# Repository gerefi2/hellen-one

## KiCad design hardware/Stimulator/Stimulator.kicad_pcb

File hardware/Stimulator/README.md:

Stimulator
==========

gerefi Stimulator

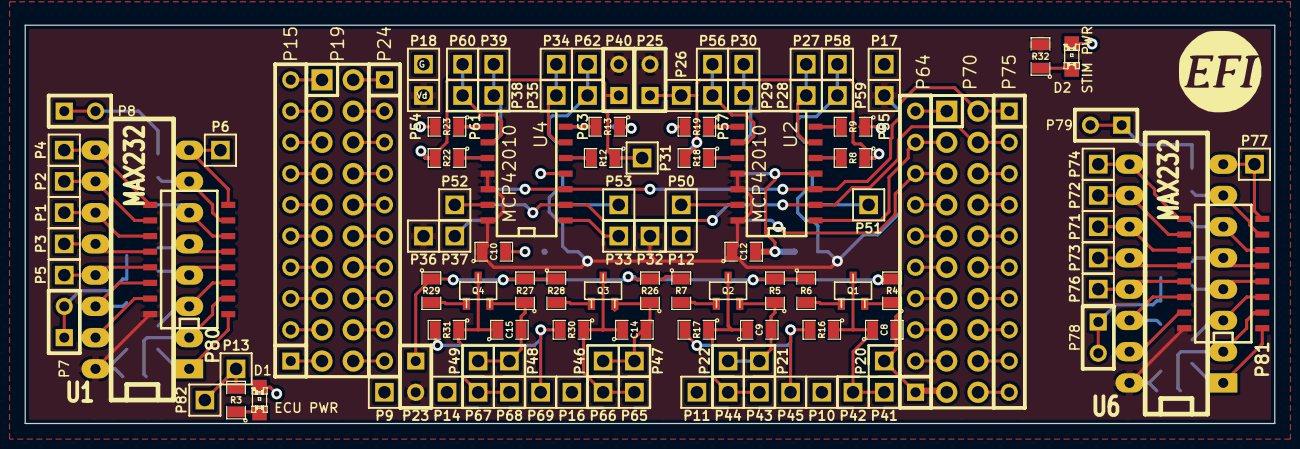
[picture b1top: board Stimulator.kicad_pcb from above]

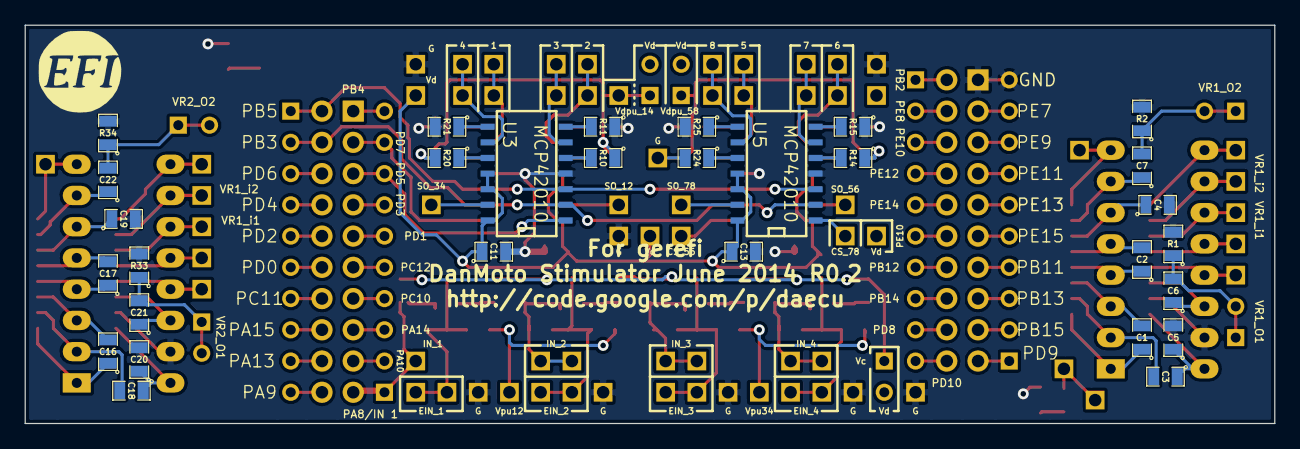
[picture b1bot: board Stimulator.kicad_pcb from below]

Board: 2 copper layers, 101.6 x 32.4 mm, 150 parts (30 on the bottom side), 122 nets.

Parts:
C1, C2, C3, C4, C5, C6, C7, C16, C17, C18, C19, C20, C21, C22: 1uF; SM0805
C8, C9, C14, C15: 100 pF; SM0805
C10, C11, C12, C13: 0.1uF; SM0805
D1: ECU PWR; LED-0805
D2: STIM PWR; LED-0805
P1, P2, P3, P4, P5, P6, P9, P10, P11, P12, P13, P14, P16, P17, P18, P20, P21, P22, P26, P27, P28, P29, P30, P31, P32, P33, P34, P35, P36, P37, P38, P39, P41, P42, P43, P44, P45, P46, P47, P48, P49, P50, P51, P52, P53, P54, P55, P56, P57, P58, P59, P60, P61, P62, P63, P65, P66, P67, P68, P69, P71, P72, P73, P74, P76, P77, P82: CONN_1; PIN_ARRAY_1
P7, P8, P23, P25, P40, P78, P79: TEST; SIL-2
P15, P24, P64, P75: CONN_10; SIL-10
P19, P70: CONN_10X2; Pin_Header_Straight_2x10
P80, P81: DIL16; SO16N
Q1, Q2, Q3, Q4: 2N7002; sot23
R1, R2, R4, R5, R6, R7, R16, R17, R26, R27, R28, R29, R30, R31, R33, R34: 10k; SM0805
R3, R32: 700R; SM0805
R8, R9, R10, R11, R12, R13, R14, R15, R18, R19, R20, R21, R22, R23, R24, R25: 0; SM0805
U1, U6: MAX232; DIP-16__300_ELL
U2, U3, U4, U5: MCP42010; SO14N

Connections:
/CS_12: P64.9, P70.3, U2.1
/CS_34: P64.8, P70.5, U3.1
/CS_56: P33.1, U4.1
/CS_78: P37.1, U5.1
/EIN_1: C8.1, P41.1, P42.1, Q1.2, R16.1
/EIN_2: C9.1, P43.1, P44.1, Q2.2, R17.1
/EIN_3: C14.1, P65.1, P66.1, Q3.2, R30.1
/EIN_4: C15.1, P67.1, P68.1, Q4.2, R31.1
/IN_1: C8.2, P20.1, P64.1, P70.19, Q1.3, R4.1
/IN_2: C9.2, P21.1, P22.1, Q2.3, R5.1
/IN_3: C14.2, P46.1, P47.1, Q3.3, R26.1
/IN_4: C15.2, P48.1, P49.1, Q4.3, R27.1
/MISO: P64.10, P70.1
/MOSI: P70.2, P75.1, U2.3, U3.3, U4.3, U5.3
/OUT1: P27.1, P28.1, U2.6
/OUT2: P56.1, P57.1, U2.9
/OUT3: P29.1, P30.1, U3.6
/OUT4: P58.1, P59.1, U3.9
/OUT5: P34.1, P35.1, U4.6
/OUT6: P60.1, P61.1, U4.9
/OUT7: P38.1, P39.1, U5.6
/OUT8: P62.1, P63.1, U5.9
/SCK: P70.4, P75.2, U2.2, U3.2, U4.2, U5.2
/U1-01: C1.1, P80.1, U1.1
/U1-02: C3.2, P80.2, U1.2
/U1-03: C1.2, P80.3, U1.3
/U1-04: C2.1, P80.4, U1.4
/U1-05: C2.2, P80.5, U1.5
/U1-06: C4.1, P80.6, U1.6
/U1-07: C7.1, P80.7, U1.7
/U1-08: P6.1, P80.8, U1.8
/U1-09: P4.1, P80.9, U1.9
/U1-12: P3.1, P80.12, U1.12
/U1-13: P5.1, P80.13, U1.13
/U1-14: C6.1, P80.14, U1.14
/U6-01: C16.1, P81.1, U6.1
/U6-02: C18.2, P81.2, U6.2
/U6-03: C16.2, P81.3, U6.3
/U6-04: C17.1, P81.4, U6.4
/U6-05: C17.2, P81.5, U6.5
/U6-06: C19.1, P81.6, U6.6
/U6-07: C22.1, P81.7, U6.7
/U6-08: P77.1, P81.8, U6.8
/U6-09: P74.1, P81.9, U6.9
/U6-12: P73.1, P81.12, U6.12
/U6-13: P76.1, P81.13, U6.13
/U6-14: C21.1, P81.14, U6.14
/VR1-O1: C6.2, P7.1, P7.2, R1.1
/VR1-O2: C7.2, P8.1, P8.2, R2.1
/VR1_i1: P1.1, P80.11, U1.11
/VR1_i2: P2.1, P80.10, U1.10
/VR2-O1: C21.2, P78.1, P78.2, R33.1
/VR2-O2: C22.2, P79.1, P79.2, R34.1
/VR2_i1: P71.1, P81.11, U6.11
/VR2_i2: P72.1, P81.10, U6.10
/Vc: P23.1, R4.2, R5.2, R6.1, R7.1, R26.2, R27.2, R28.1, R29.1
/Vd: C3.1, C5.1, C10.1, C11.1, C12.1, C13.1, C18.1, C20.1, P23.2, P25.2, P32.1, P36.1, P40.2, P54.1, P55.1, P80.16, P81.16, R32.2, U1.16, U2.11, U2.12, U2.14, U3.11, U3.12, U3.14, U4.11, U4.12, U4.14, U5.11, U5.12, U5.14, U6.16
/Vdpu_14: P25.1, P26.1, R8.1, R10.1, R18.2, R20.2
/Vdpu_58: P31.1, P40.1, R12.1, R14.1, R22.2, R24.2
/Vipu12: P45.1, R16.2, R17.2
/Vipu34: P69.1, R30.2, R31.2
GND: C4.2, C5.2, C10.2, C11.2, C12.2, C13.2, C19.2, C20.2, D1.2, D2.2, P9.1, P10.1, P11.1, P12.1, P14.1, P15.10, P16.1, P17.1, P18.1, P19.1, P80.15, P81.15, R1.2, R2.2, R9.1, R11.1, R13.1, R15.1, R19.2, R21.2, R23.2, R25.2, R33.2, R34.2, U1.15, U2.4, U3.4, U4.4, U5.4, U6.15
unnamed: P70.6, P75.3
unnamed: P70.20, P75.10
unnamed: P64.2, P70.17
unnamed: P64.3, P70.15
unnamed: P64.4, P70.13
unnamed: P64.5, P70.11
unnamed: P64.6, P70.9
unnamed: P64.7, P70.7
unnamed: P70.18, P75.9
unnamed: P70.8, P75.4
unnamed: P70.10, P75.5
unnamed: P70.12, P75.6
unnamed: P70.14, P75.7
unnamed: P70.16, P75.8
unnamed: P15.5, P19.11
unnamed: P19.4, P24.2
unnamed: P19.6, P24.3
unnamed: P19.8, P24.4
unnamed: P19.10, P24.5
unnamed: P19.12, P24.6
unnamed: P19.14, P24.7
unnamed: P19.16, P24.8
unnamed: P19.18, P24.9
unnamed: P19.20, P24.10
unnamed: P15.1, P19.19
unnamed: P15.2, P19.17
unnamed: P15.3, P19.15
unnamed: P15.4, P19.13
unnamed: P15.6, P19.9
unnamed: P15.7, P19.7
unnamed: P15.8, P19.5
unnamed: P15.9, P19.3
unnamed: P19.2, P24.1
unnamed: R14.2, U5.5
unnamed: R15.2, U5.7
unnamed: R25.1, U5.8
unnamed: R24.1, U5.10
unnamed: P50.1, U2.13
unnamed: P52.1, U4.13
unnamed: P51.1, U3.13
unnamed: P53.1, U5.13
unnamed: P13.1, P82.1, R3.2
unnamed: D2.1, R32.1
unnamed: D1.1, R3.1
unnamed: R8.2, U2.5
unnamed: R9.2, U2.7
unnamed: R19.1, U2.8
unnamed: R18.1, U2.10
unnamed: R10.2, U3.5
unnamed: Q3.1, R28.2
unnamed: Q2.1, R7.2
unnamed: Q4.1, R29.2
unnamed: R11.2, U3.7
unnamed: R21.1, U3.8
unnamed: R20.1, U3.10
unnamed: R12.2, U4.5
unnamed: R13.2, U4.7
unnamed: R23.1, U4.8
unnamed: R22.1, U4.10
unnamed: Q1.1, R6.2

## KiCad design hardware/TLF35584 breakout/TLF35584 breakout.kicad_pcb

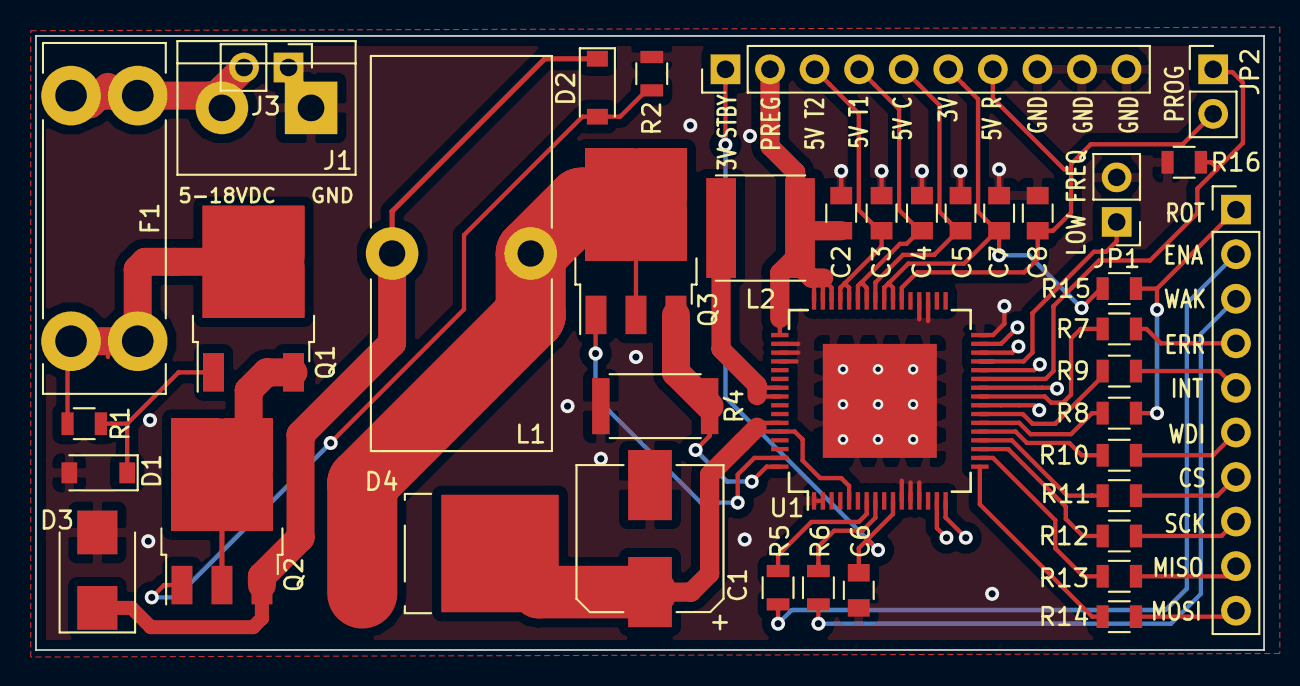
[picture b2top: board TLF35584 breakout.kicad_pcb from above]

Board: 2 copper layers, 70.0 x 35.0 mm, 40 parts (0 on the bottom side), 41 nets.

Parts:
C1: 100uF/50V; CP_Elec_8x10.5
C2, C5, C7: 22uF/16V; C_0805
C3, C4, C6, C8: 4.7uF/16V; C_0805
D1, D2: BZT52C18; D_SOD-123
D3: SMBJ24A; D_SMB
D4: MBRD835LT4G; DPAK_Diode
F1: 5A Fuse; Fuseholder_blade
J1: POWER_IN; TerminalBlock_bornier-2_P5.08mm
J2: SIGNALS; Pin_Header_Straight_1x10_Pitch2.54mm
J3: POWER_IN; Pin_Header_Straight_1x02_Pitch2.54mm
J4: POWER_OUT; Pin_Header_Straight_1x10_Pitch2.54mm
JP1: FRE; Pin_Header_Straight_1x02_Pitch2.54mm
JP2: MPS; Pin_Header_Straight_1x02_Pitch2.54mm
L1: 22uH/8A; L_Toroid_Vertical_L22.4mm_W10.2mm_P7.90mm_Vishay_TJ4
L2: 4.7uH/3A; 6.0X6.0X3.0
Q1: DN2625K4; TO-252-2
Q2: NTD2955T4G; TO-252-3_TabPin2
Q3: NTD20N06LT4G; TO-252-3_TabPin2
R1: 100K; R_0805
R2: 39K; R_0805
R4: 0.03R; R_2512
R5, R6, R7, R8, R9, R10, R11, R12, R13, R14: 1K; R_0805
R15, R16: 10K; R_0805
U1: TLF35584QKVS2; LQFP-64-1EP_10x10mm_Pitch0.5mm

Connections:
/3.3V_STBY: C6.1, J4.1, U1.10
/3.3V_UC: C7.1, J4.6, R15.1, U1.39, U1.40
/5V_COMMS: C5.1, J4.5, U1.41
/5V_REF: C8.1, J4.7, JP2.2, U1.38
/5V_TRACKER1: C3.1, J4.3, U1.44, U1.45
/5V_TRACKER2: C4.1, J4.4, U1.42, U1.43
/12V_BAT: F1.2, J1.2, J3.2
/ENABLE: J2.2, R5.1
/ERR: J2.4, R7.2
/INT: J2.5, R9.2
/ROT: J2.1, R8.2, R15.2
/SPI_CS: J2.7, R11.2
/SPI_MISO: J2.9, R13.2
/SPI_MOSI: J2.10, R14.2
/SPI_SCK: J2.8, R12.2
/VST: C1.1, D4.1, U1.5, U1.59, U1.60
/V_PREREG: C2.2, J4.2, L2.2, U1.46, U1.47, U1.48, U1.49
/WAKE: J2.3, R6.1
/WDI: J2.6, R10.2
GND: C1.2, C2.1, C3.2, C4.2, C5.2, C6.2, C7.2, C8.2, D1.2, D3.2, J1.1, J3.1, J4.8, J4.9, J4.10, JP1.2, R2.2, R4.1, R16.2, U1.1, U1.2, U1.11, U1.12, U1.13, U1.28, U1.32, U1.35, U1.36, U1.50, U1.51, U1.52, U1.65
unnamed: D1.1, Q1.1, R1.2
unnamed: D2.1, D3.1, L1.2, Q2.3
unnamed: D2.2, Q2.1, R2.1
unnamed: D4.2, L1.1, Q3.2
unnamed: F1.1, Q1.2, R1.1
unnamed: JP1.1, U1.29
unnamed: JP2.1, R16.1, U1.27
unnamed: L2.1, U1.55, U1.56
unnamed: Q1.3, Q2.2
unnamed: Q3.1, U1.63
unnamed: Q3.3, R4.2, U1.64
unnamed: R5.2, U1.7
unnamed: R6.2, U1.8
unnamed: R7.1, U1.25
unnamed: R8.1, U1.22
unnamed: R9.1, U1.23
unnamed: R10.1, U1.21
unnamed: R11.1, U1.20
unnamed: R12.1, U1.19
unnamed: R13.1, U1.18
unnamed: R14.1, U1.17

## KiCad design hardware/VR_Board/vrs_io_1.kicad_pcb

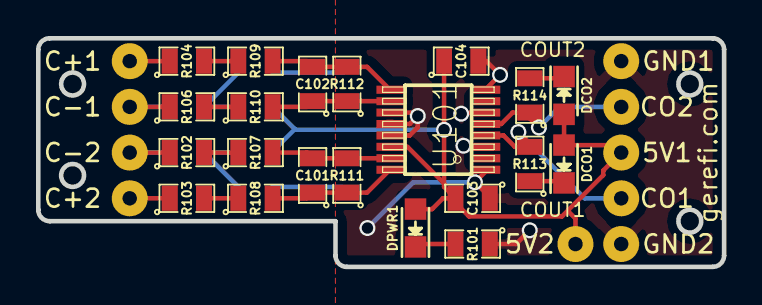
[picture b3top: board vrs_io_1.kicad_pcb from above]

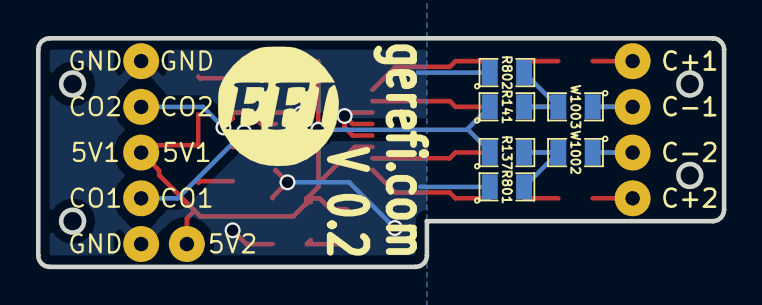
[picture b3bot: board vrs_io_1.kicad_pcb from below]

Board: 2 copper layers, 38.1 x 12.7 mm, 38 parts (11 on the bottom side), 21 nets.

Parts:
5V1, 5V2: CONN_01X01; SolderWirePad_single_0-8mmDrill
C101, C102: 1000pF; SM0805
C103: 10uF; SM0805
C104: 0.1uF; SM0805
C+1, C+2: CONN_01X01; SolderWirePad_single_0-8mmDrill
C-1, C-2: CONN_01X01; SolderWirePad_single_0-8mmDrill
CO1, CO2: CONN_01X01; SolderWirePad_single_0-8mmDrill
DCO1, DCO2: LED-red; LED_0805
DPWR1: LED-red; LED_0805
G?: LOGO; LOGO_F
GND1, GND2: CONN_01X01; SolderWirePad_single_0-8mmDrill
R101, R113, R114: 10k; SM0805
R102, R103, R104, R106, R107, R108, R109, R110, R111, R112: 5k; SM0805
R137, R141: 1K; SM0805
R801, R802: pdwn; SM0805
U101: MAX9926/9927; maxim-10-QSOP16
W1002, W1003: JMP; SM0805

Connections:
/5V: 5V1.1, 5V2.1, C103.2, C104.1, DCO1.2, DCO2.2, DPWR1.2, R137.1, R141.1, U101.14
/CAM+: C+1.1, R104.1
/CAM-: C-1.1, R106.1, W1003.1
/CRK2+: C+2.1, R103.1
/CRK2-: C-2.1, R102.1, W1002.1
/Cout1: CO1.1, R113.2, U101.4
/Cout2: CO2.1, R114.1, U101.5
GND: C103.1, C104.2, GND1.1, GND2.1, R101.1, R801.1, R802.1, U101.1, U101.3, U101.6, U101.8, U101.11, U101.12, U101.13
unnamed: C101.1, R108.2, R111.1, U101.16
unnamed: C101.2, R107.2, R111.2, U101.15
unnamed: C102.1, R110.2, R112.1, U101.10
unnamed: C102.2, R109.2, R112.2, U101.9
unnamed: DCO1.1, R113.1
unnamed: DCO2.1, R114.2
unnamed: DPWR1.1, R101.2
unnamed: R102.2, R107.1
unnamed: R103.2, R108.1
unnamed: R104.2, R109.1
unnamed: R106.2, R110.1
unnamed: R137.2, R801.2, W1002.2
unnamed: R141.2, R802.2, W1003.2

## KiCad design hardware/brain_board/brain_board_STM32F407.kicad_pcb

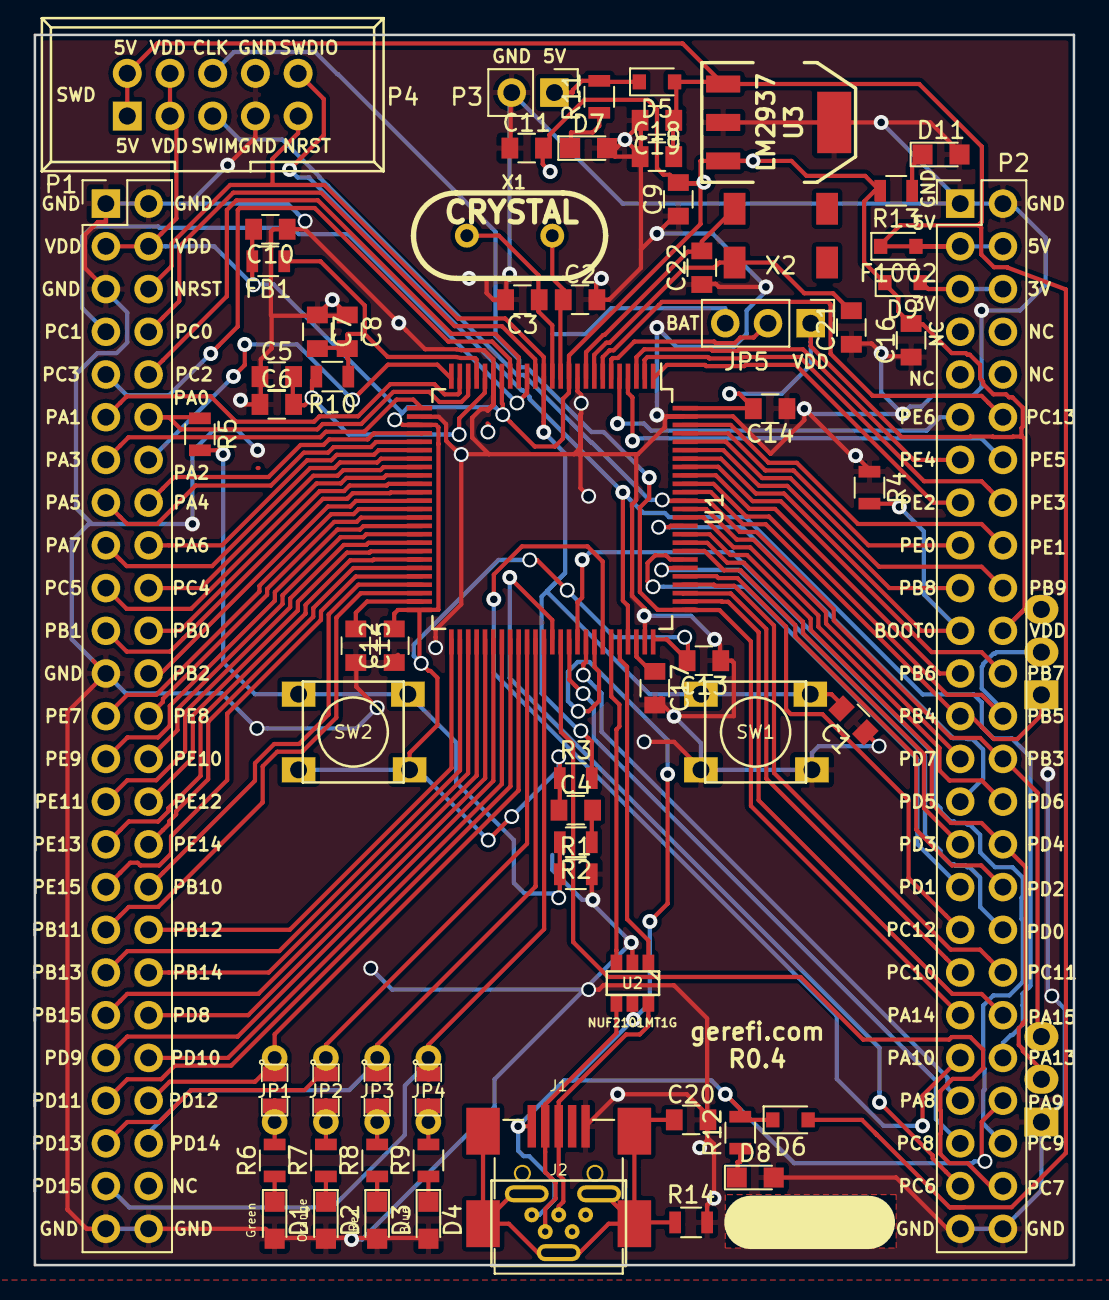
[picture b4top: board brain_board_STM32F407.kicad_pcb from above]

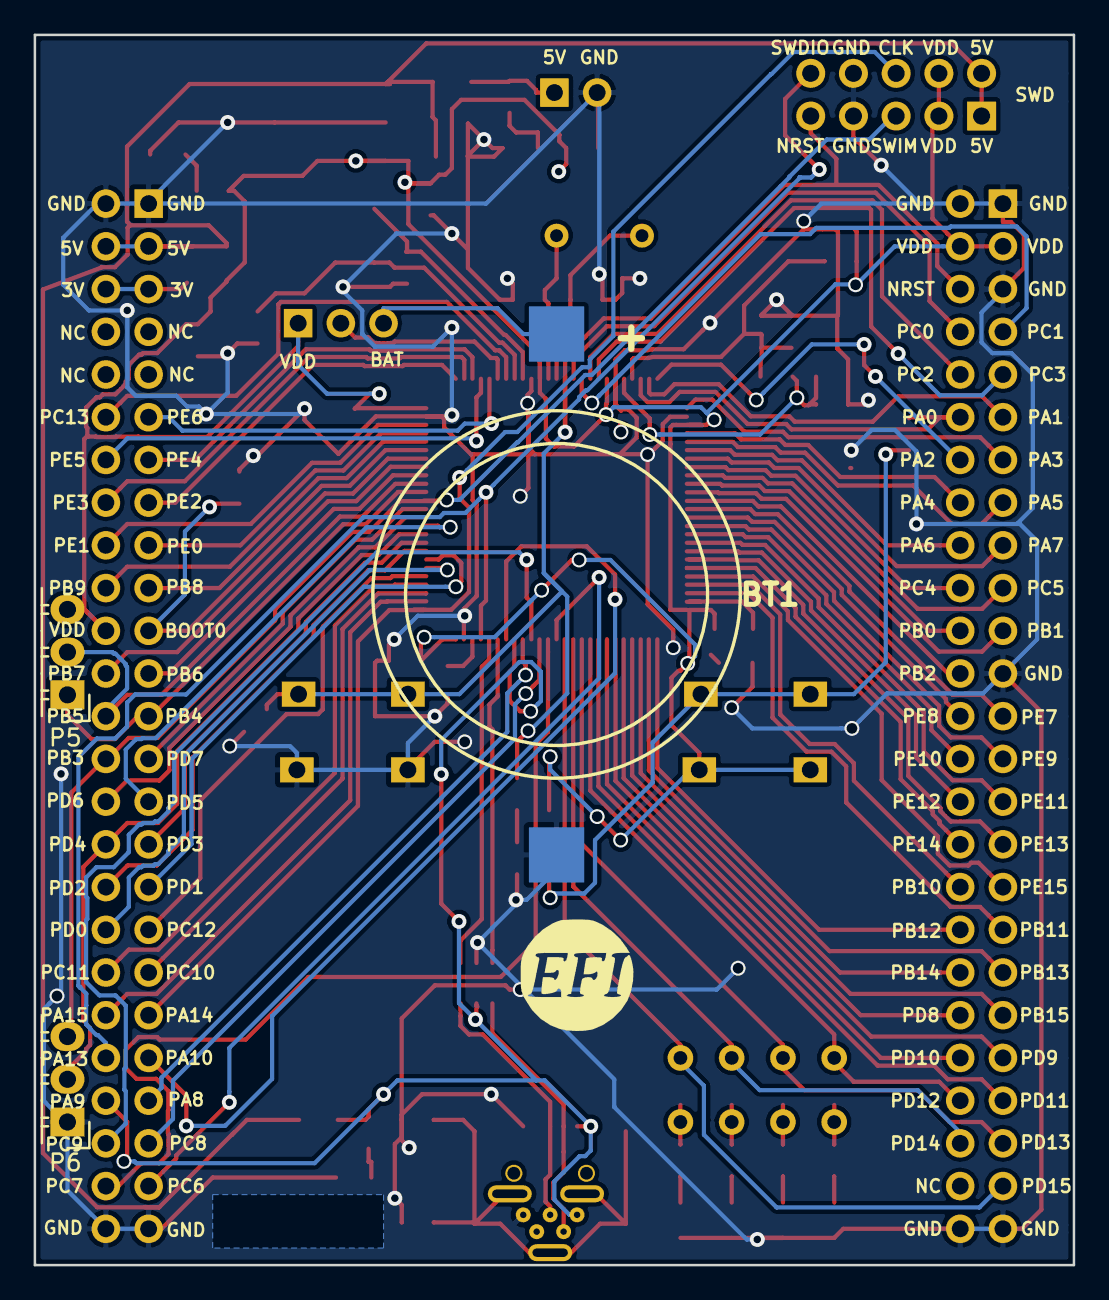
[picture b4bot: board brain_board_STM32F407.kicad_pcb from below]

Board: 2 copper layers, 61.8 x 73.2 mm, 70 parts (4 on the bottom side), 111 nets.

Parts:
BT1: BATTERY_CR2032; BATT_CR2032_MPD
C1: 20nF; C_0805
C2, C3, C21, C22: 18pF; C_0805
C4, C15, C17: 2u2F; C_0805
C5, C8: 0.01uF; C_0805
C6, C7, C16: 1uF; C_0805
C9, C10, C11, C12, C13, C14, C18, C20: 0.1uF; C_0805
C19: 4.7uF; C_0805
D1, D2, D3, D4, D7, D8, D11: BLUE_LED_0805; LED_0805
D5, D6, D9: PMEG2010EA; D_0805
F1002: FUSE; D_0805
FB1: FILTER; R_0805
G1: LOGO; LOGO_F
J1: MINI-USB-5P-3400020P1
J2: MINI-USB-5P-3400020P1V; MINI-USB_RCTP_V-T_B
JP1, JP2, JP3, JP4: JUMPER; SM0805_jumper
JP5: JUMPER3; Pin_Header_Straight_1x03_Pitch2.54mm
P1, P2: CONN_25X2; Pin_Header_Straight_2x25_Pitch2.54mm
P3: CONN_2; Pin_Header_Straight_1x02_Pitch2.54mm
P4: CONN_02X05; IDC_Header_Straight_10pins
P5, P6: CONN_01X03; Pin_Header_Angled_1x03
R1, R3, R4: 10k; R_0805
R2: 100R; R_0805
R5: 330R; R_0805
R6, R7, R8, R9: 680R; R_0805
R10: 47R; R_0805
R11, R12, R13: 1k; R_0805
R14: 100k; R_0805
SW1, SW2: SW_PUSH; TL-1105
U1: STM32F407VG; LQFP-100_14x14mm_Pitch0.5mm
U2: NUF2101MT1G; SOT-457
U3: LM2937; SOT223
X1: CRYSTAL; HC-49V
X2: CRYSTAL(MC306); MC-306

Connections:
/3V: D9.2, P2.5, P2.6
/5V: C18.2, C19.1, D5.2, D6.2, F1002.1, F1002.2, P2.3, P2.4, P4.1, P4.2, U3.1
/BOOT0: P2.21, R4.2, U1.94
/D+: J1.3, J2.3, U2.6
/D-: J1.2, J2.2, U2.4
/NRST: C1.2, P1.6, P4.9, R3.2, SW1.1, U1.14
/PA0: P1.12, R5.1, U1.23
/PA1: P1.11, U1.24
/PA2: P1.14, U1.25
/PA3: P1.13, U1.26
/PA4: P1.16, U1.29
/PA5: P1.15, U1.30
/PA6: P1.18, U1.31
/PA7: P1.17, U1.32
/PA8: P2.43, U1.67
/PA9: D6.1, J1.1, J2.1, P2.44, R12.2, U1.68, U2.5
/PA10: P2.41, U1.69
/PA11: U1.70, U2.3
/PA12: U1.71, U2.1
/PA13: P2.42, P4.10, U1.72
/PA14: P2.39, P4.6, U1.76
/PA15: P2.40, U1.77
/PB0: P1.22, U1.35
/PB1: P1.21, U1.36
/PB2: P1.24, U1.37
/PB3: P2.28, P4.5, P6.3, U1.89
/PB4: P2.25, P5.1, U1.90
/PB5: P2.26, P5.2, U1.91
/PB6: P2.23, U1.92
/PB7: P2.24, U1.93
/PB8: P2.19, U1.95
/PB9: P2.20, U1.96
/PB10: P1.34, U1.47
/PB11: P1.35, U1.48
/PB12: P1.36, U1.51
/PB13: P1.37, U1.52
/PB14: P1.38, U1.53
/PB15: P1.39, U1.54
/PC0: P1.8, U1.15
/PC1: P1.7, U1.16
/PC2: P1.10, U1.17
/PC3: P1.9, U1.18
/PC4: P1.20, U1.33
/PC5: P1.19, U1.34
/PC6: P2.47, U1.63
/PC7: P2.48, U1.64
/PC8: P2.45, U1.65
/PC9: P2.46, U1.66
/PC10: P2.37, U1.78
/PC11: P2.38, U1.79
/PC12: P2.35, U1.80
/PC13: P2.12, U1.7
/PD0: P2.36, U1.81
/PD1: P2.33, U1.82
/PD2: P2.34, U1.83
/PD3: P2.31, U1.84
/PD4: P2.32, P6.2, U1.85
/PD5: P2.29, U1.86
/PD6: P2.30, U1.87
/PD7: P2.27, U1.88
/PD8: P1.40, U1.55
/PD9: P1.41, U1.56
/PD10: P1.42, U1.57
/PD11: P1.43, U1.58
/PD12: JP1.1, P1.44, U1.59
/PD13: JP2.1, P1.45, U1.60
/PD14: JP3.1, P1.46, U1.61
/PD15: JP4.1, P1.47, U1.62
/PE0: P2.17, U1.97
/PE1: P2.18, U1.98
/PE2: P2.15, U1.1
/PE3: P2.16, U1.2
/PE4: P2.13, U1.3
/PE5: P2.14, U1.4
/PE6: P2.11, U1.5
/PE7: P1.25, U1.38
/PE8: P1.26, U1.39
/PE9: P1.27, U1.40
/PE10: P1.28, U1.41
/PE11: P1.29, U1.42
/PE12: P1.30, U1.43
/PE13: P1.31, U1.44
/PE14: P1.32, U1.45
/PE15: P1.33, U1.46
/Shield: C20.1, J1.6, J2.6, R14.1
/VDD: C4.1, C9.2, C10.2, C11.2, C12.2, C13.2, C14.2, C16.2, D9.1, FB1.2, JP5.1, P1.3, P1.4, P2.22, P4.3, P4.4, P5.3, R3.1, R13.2, SW2.2, U1.11, U1.19, U1.28, U1.50, U1.75, U1.100, U3.3
GND: BT1.2, C1.1, C2.2, C3.2, C5.1, C6.1, C7.1, C8.1, C9.1, C10.1, C11.1, C12.1, C13.1, C14.1, C15.2, C16.1, C17.2, C18.1, C19.2, C20.2, C21.1, C22.1, D1.2, D2.2, D3.2, D4.2, D7.2, D8.2, D11.2, J1.5, J2.5, P1.1, P1.2, P1.5, P1.23, P1.49, P1.50, P2.1, P2.2, P2.49, P2.50, P3.2, P4.7, P4.8, P6.1, R1.2, R4.1, R14.2, SW1.2, U1.10, U1.20, U1.27, U1.74, U1.99, U2.2, U3.2, U3.4
unnamed: BT1.1, JP5.3
unnamed: C2.1, U1.12, X1.2
unnamed: C3.1, U1.13, X1.1
unnamed: C4.2, R2.1
unnamed: C5.2, C6.2, R10.2, U1.21
unnamed: C7.2, C8.2, FB1.1, R10.1, U1.22
unnamed: C15.1, U1.49
unnamed: C17.1, U1.73
unnamed: C21.2, U1.8, X2.1
unnamed: C22.2, U1.9, X2.4
unnamed: D1.1, R6.1
unnamed: D2.1, R7.1
unnamed: D3.1, R8.1
unnamed: D4.1, R9.1
unnamed: D5.1, P3.1, R11.2
unnamed: D7.1, R11.1
unnamed: D8.1, R12.1
unnamed: D11.1, R13.1
unnamed: JP1.2, R6.2
unnamed: JP2.2, R7.2
unnamed: JP3.2, R8.2
unnamed: JP4.2, R9.2
unnamed: JP5.2, U1.6
unnamed: R1.1, R2.2, R5.2, SW2.1

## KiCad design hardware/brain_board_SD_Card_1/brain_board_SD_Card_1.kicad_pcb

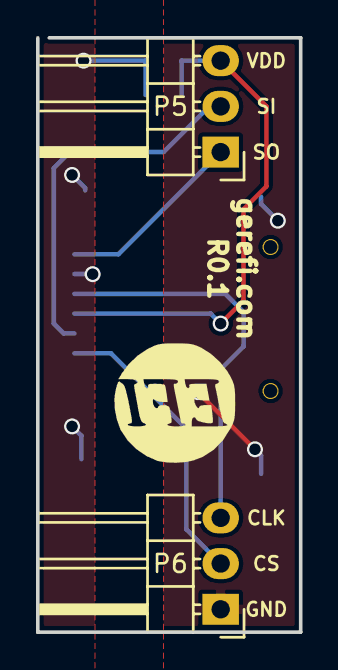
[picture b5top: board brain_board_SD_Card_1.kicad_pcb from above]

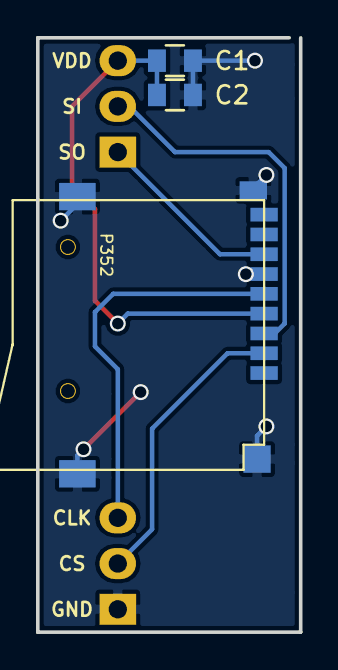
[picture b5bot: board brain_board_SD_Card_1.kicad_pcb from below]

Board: 2 copper layers, 14.6 x 33.0 mm, 6 parts (3 on the bottom side), 6 nets.

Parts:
C1: 1000pF; C_0805
C2: 0.1uF; C_0805
G1: LOGO; LOGO_F
P5, P6: CONN_01X03; Pin_Header_Angled_1x03
P352: MICRO-SDCARD-CONNECTOR-3300060P1

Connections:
/3.3V: C1.2, C2.2, P5.3, P352.4
/CS_SD_MODULE: P6.2, P352.2
/SPI_MISO: P5.1, P352.7
/SPI_MOSI: P5.2, P352.3
/SPI_SCK: P6.3, P352.5
GND: C1.1, C2.1, P6.1, P352.6, P352.G1, P352.G2, P352.G3, P352.G4

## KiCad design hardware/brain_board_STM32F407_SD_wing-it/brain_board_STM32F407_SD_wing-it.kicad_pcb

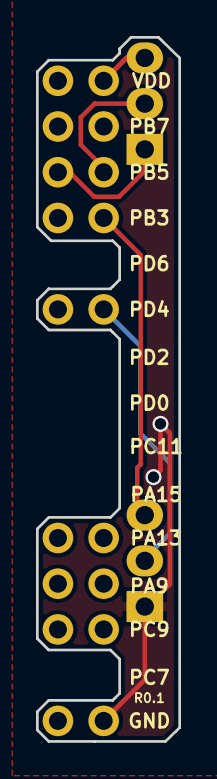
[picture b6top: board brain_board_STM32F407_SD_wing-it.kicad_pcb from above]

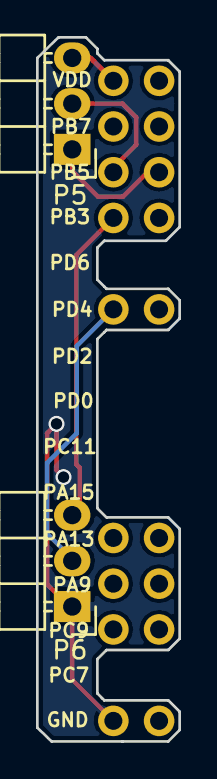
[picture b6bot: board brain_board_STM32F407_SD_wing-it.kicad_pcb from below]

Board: 2 copper layers, 7.9 x 39.1 mm, 8 parts (2 on the bottom side), 6 nets.

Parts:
P1: CONN_02X04; Pin_Header_Straight_2x04_Pitch2.54mm
P2: CONN_02X03; Pin_Header_Straight_2x03_Pitch2.54mm
P5, P6: CONN_01X03; Pin_Header_Angled_1x03
P7, P8, P11, P12: CONN_01X01; Pin_Header_Straight_1x01_Pitch2.54mm

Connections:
/PB3: P1.8, P6.3
/PB4: P1.5, P5.1
/PB5: P1.6, P5.2
/PD4: P6.2, P7.1
/VDD: P1.2, P5.3
GND: P6.1, P8.1

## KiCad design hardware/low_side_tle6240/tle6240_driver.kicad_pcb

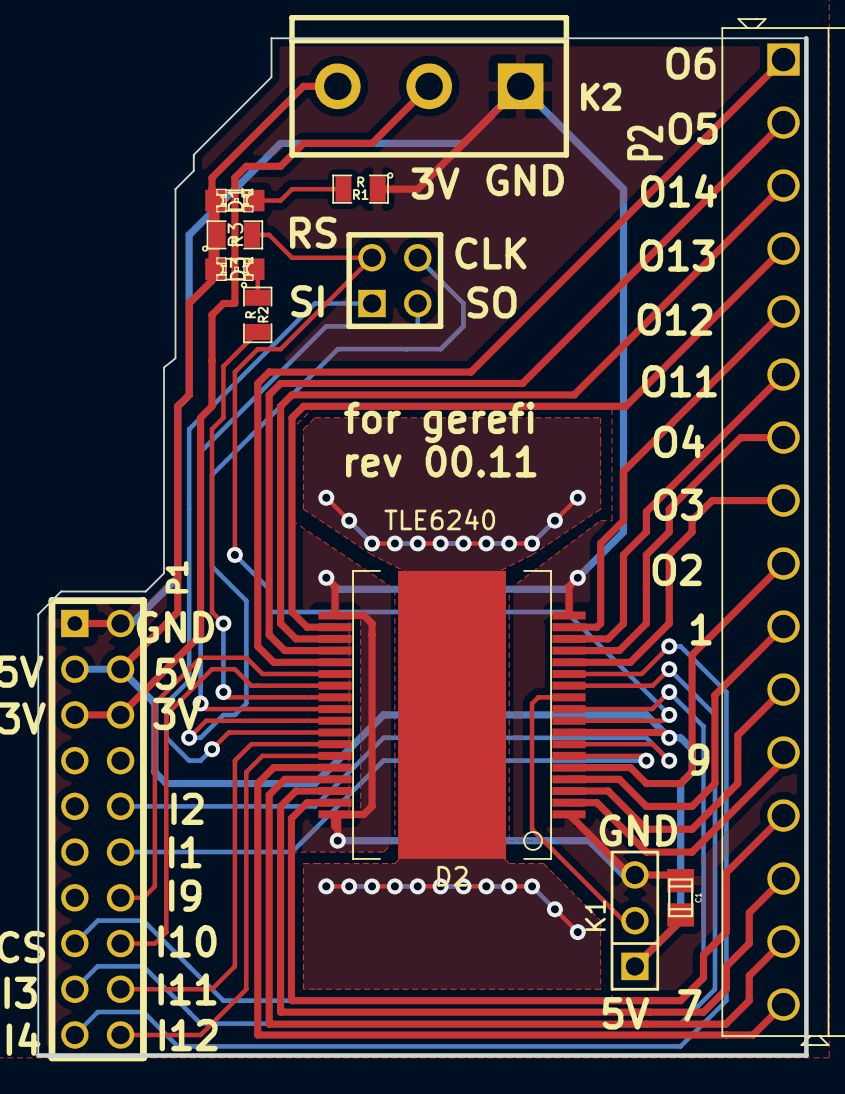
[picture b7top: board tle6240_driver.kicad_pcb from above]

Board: 2 copper layers, 42.7 x 56.5 mm, 12 parts (0 on the bottom side), 36 nets.

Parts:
C1: C; c_0805
D1, D3: LED; LED-0805
D2: TLE6240; PG-DSO-36
K1: JUMPER3; PIN_ARRAY_3X1
K2: CONN_3; bornier3
P1: CONN_10X2; PIN_ARRAY_10X2
P2: CONN_16; SIL-16_3.5MM
P3: CONN_2X2; PIN_ARRAY_2X2
R1, R2, R3: R; SM0805

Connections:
+5V: C1.1, D1.1, D2.8, D3.1, K1.1, K2.3, P1.3, P1.4, R3.1
/+3.3V: K2.2, P1.5, P1.6
/CS: D2.10, P1.15
/Fault: D2.26, R2.2
/IN1: D2.6, P1.12
/IN2: D2.7, P1.10
/IN3: D2.12, P1.17
/IN4: D2.13, P1.19
/IN9: D2.24, P1.14
/IN10: D2.25, P1.16
/IN11: D2.30, P1.18
/IN12: D2.31, P1.20
/OUT1: D2.4, P2.10
/OUT2: D2.5, P2.9
/OUT3: D2.14, P2.8
/OUT4: D2.15, P2.7
/OUT5: D2.22, P2.2
/OUT6: D2.23, P2.1
/OUT7: D2.32, P2.16
/OUT8: D2.33, P2.15
/OUT9: D2.2, P2.12
/OUT10: D2.3, P2.11
/OUT11: D2.16, P2.6
/OUT12: D2.17, P2.5
/OUT13: D2.20, P2.4
/OUT14: D2.21, P2.3
/OUT15: D2.34, P2.14
/OUT16: D2.35, P2.13
/PRG: D2.11, K1.2
/Reset: D2.9, P3.2, R3.2
/SCLK: D2.28, P3.4
/SI: D2.29, P3.1
/SO: D2.27, P3.3
GND: C1.2, D2.1, D2.18, D2.19, D2.36, K1.3, K2.1, P1.1, P1.2, R1.1
unnamed: D3.2, R2.1
unnamed: D1.2, R1.2

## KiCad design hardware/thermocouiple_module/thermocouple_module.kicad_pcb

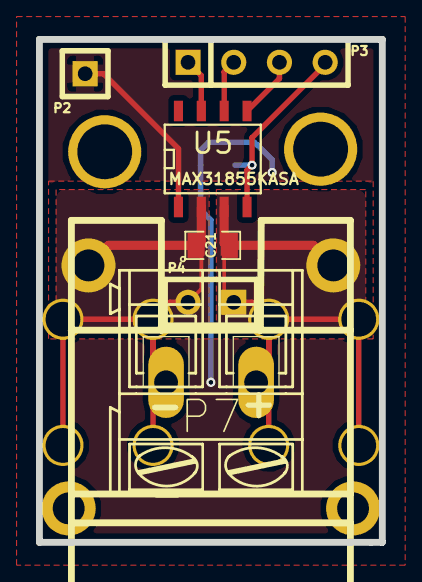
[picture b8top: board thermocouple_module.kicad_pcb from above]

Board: 2 copper layers, 19.0 x 27.9 mm, 12 parts (1 on the bottom side), 7 nets.

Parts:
C8: 100nF; SM0805-SM0603
C21: 10nF; SM0805-SM0603
P1: CONN_2; tcpl_PCC-SMP
P2: CONN_1; SIL-1
P3: CONN_4; SIL-4
P4: CONN_2; SIL-2
P5, P6: CONN_1; SCREW_TERM_534-7693
P7: CONN_2; AK300-2
U5: MAX31855KASA; SO8E
V801, V802: VIA; 1pin

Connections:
3.3v: C8.1, P3.4, U5.4
//CS: P3.2, U5.6
/MISO: P3.1, U5.7
/SCK: P3.3, U5.5
/TCPL+: C21.2, P1.2, P4.1, P6.1, P7.1, U5.3
/TCPL-: C21.1, P1.1, P4.2, P5.1, P7.2, U5.2
GND: C8.2, P2.1, U5.1
